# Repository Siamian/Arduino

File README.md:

# List of Arduino programs:
- Blinking RGB LEDs for Christmas decoration
- Weather station

# Code editor used to write programs:
- Arduino IDE

# Microcontrollers used:
- AVR ATmega328-PU
- AVR ATtiny13A-PU

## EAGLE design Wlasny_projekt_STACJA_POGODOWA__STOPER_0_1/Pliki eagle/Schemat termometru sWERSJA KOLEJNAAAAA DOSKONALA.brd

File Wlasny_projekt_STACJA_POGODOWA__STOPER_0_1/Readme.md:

# do dokonczenia

Inline-style: 

Reference-style: 
![alt text][logo]

[logo]: https://github.com/Siamian/Arduino-projects/blob/main/Wlasny_projekt_STACJA_POGODOWA__STOPER_0_1/PXL_20221018_163713476.jpg "Logo Title Text 2"

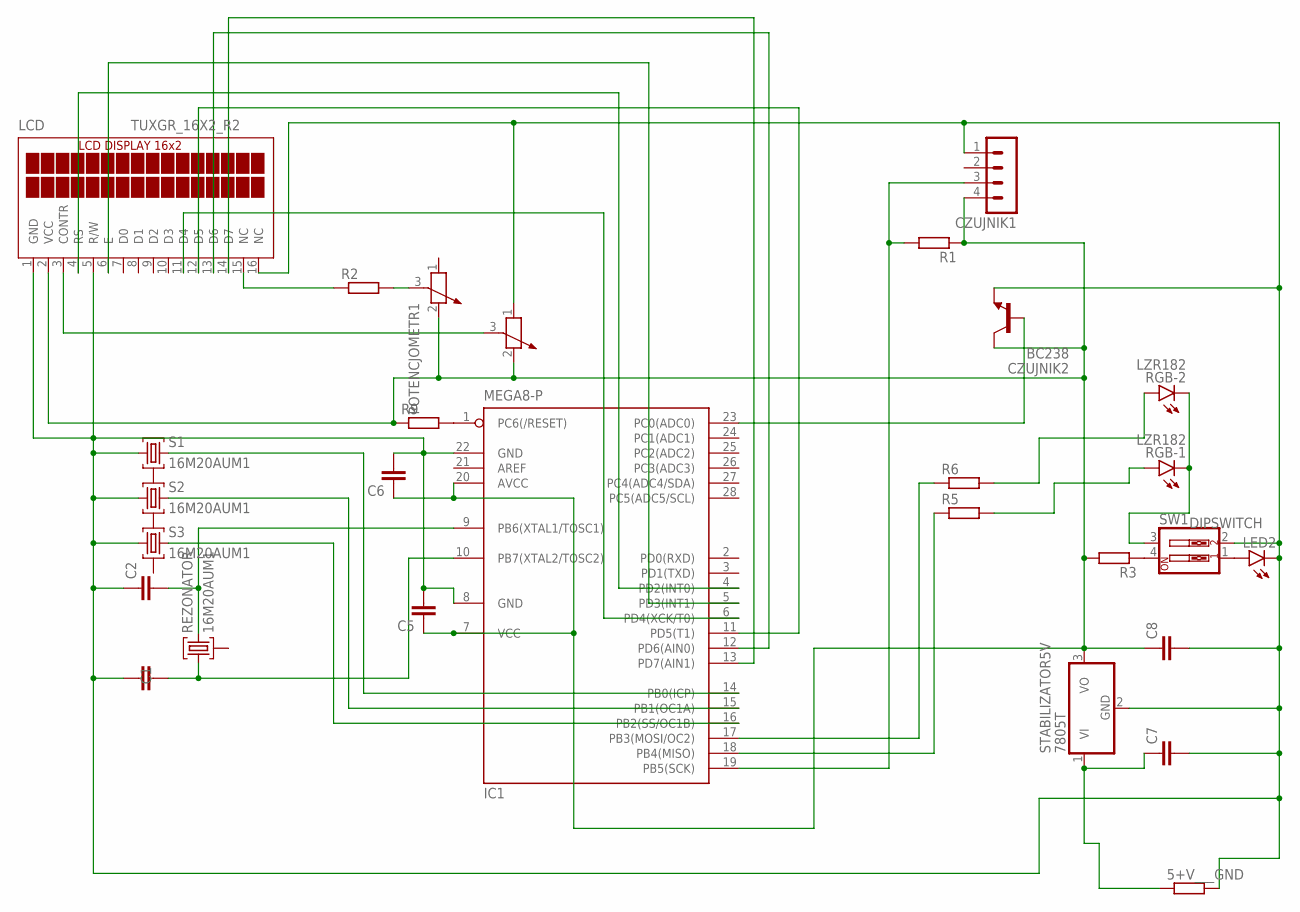
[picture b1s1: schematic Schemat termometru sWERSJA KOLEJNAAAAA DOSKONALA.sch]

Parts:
5+V___GND: R-EU_0207/10; 0207/10
C1, C2, C5, C6, C7, C8: C-EU025-040X050; C025-040X050
CZUJNIK1: MA04-1
CZUJNIK2: BC238; TO92
IC1: MEGA8-P; DIL28-3
LCD: TUXGR_16X2_R2
LED2: LED5MM
POTENCJOMETR1, POTENCJOMETR2: POTENTIOMETER_PT-10; PT-10
R1, R2, R3, R5, R6, R9: R-EU_0207/10; 0207/10
REZONATOR: 16M20AUM1; UM1
RGB: LZR182
S1, S2, S3: 16M20AUM1; UM1
STABILIZATOR5V: 7805T; TO220H
SW1: SW_DIP-2; EDG-02

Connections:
DIPSWITCH: RGB.K1 (C), RGB.K2 (C), SW1.3
unnamed: R3.1, SW1.4
unnamed: IC1.18 (PB4(MISO)), R5.1
unnamed: R5.2, RGB.A1 (A)
unnamed: CZUJNIK2.2 (B), IC1.23 (PC0(ADC0))
unnamed: CZUJNIK1.3, IC1.19 (PB5(SCK)), R1.2
unnamed: IC1.16 (PB2(SS/OC1B)), S3.3
unnamed: IC1.15 (PB1(OC1A)), S2.3
unnamed: IC1.14 (PB0(ICP)), S1.3
unnamed: POTENCJOMETR1.3, R2.2
unnamed: LED2.A, SW1.1
unnamed: LCD.15 (NC), R2.1
unnamed: IC1.17 (PB3(MOSI/OC2)), R6.1
unnamed: LCD.3 (CONTR), POTENCJOMETR2.3
unnamed: R6.2, RGB.A2 (A)
unnamed: C2.2, IC1.9 (PB6(XTAL1/TOSC1)), REZONATOR.3
unnamed: IC1.4 (PD2(INT0)), LCD.4 (RS)
unnamed: C1.2, IC1.10 (PB7(XTAL2/TOSC2)), REZONATOR.1
unnamed: C5.1, C6.1, C8.1, CZUJNIK1.4, CZUJNIK2.3 (C), IC1.7 (VCC), IC1.20 (AVCC), LCD.2 (VCC), POTENCJOMETR1.2, POTENCJOMETR2.2, R1.1, R3.2, R9.1, STABILIZATOR5V.3 (VO)
unnamed: 5+V___GND.2, C1.1, C2.1, C5.2, C6.2, C7.2, C8.2, CZUJNIK1.1, CZUJNIK2.1 (E), IC1.8 (GND), IC1.22 (GND), LCD.1 (GND), LCD.5 (R/W), LCD.16 (NC), LED2.K (C), POTENCJOMETR2.1, S1.1, S2.1, S3.1, STABILIZATOR5V.2 (GND), SW1.2
unnamed: IC1.1 (PC6(/RESET)), R9.2
unnamed: IC1.5 (PD3(INT1)), LCD.6 (E)
unnamed: IC1.13 (PD7(AIN1)), LCD.14 (D7)
unnamed: IC1.12 (PD6(AIN0)), LCD.13 (D6)
unnamed: IC1.11 (PD5(T1)), LCD.12 (D5)
unnamed: IC1.6 (PD4(XCK/T0)), LCD.11 (D4)
unnamed: 5+V___GND.1, C7.1, STABILIZATOR5V.1 (VI)

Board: 2 copper layers, 27 parts (0 on the bottom side), 27 nets, no tracks yet.
